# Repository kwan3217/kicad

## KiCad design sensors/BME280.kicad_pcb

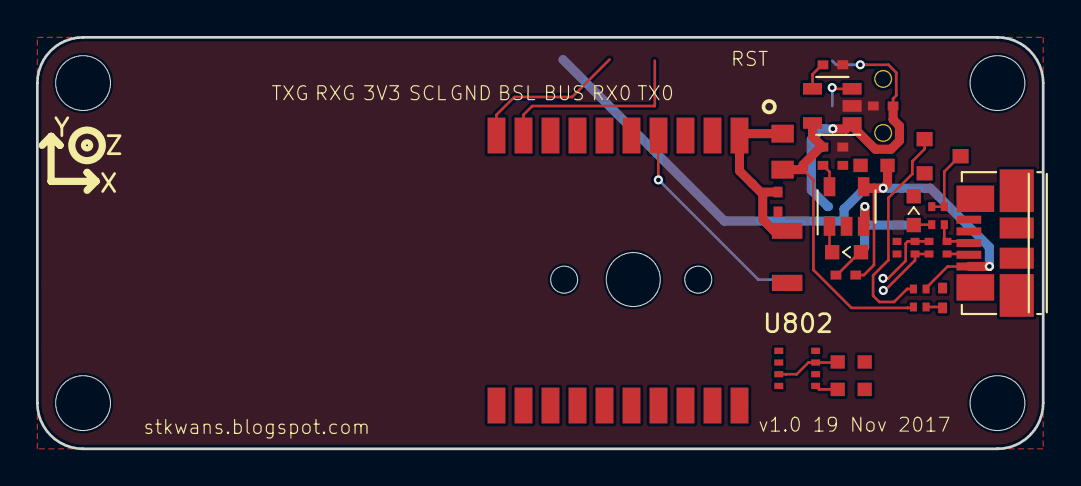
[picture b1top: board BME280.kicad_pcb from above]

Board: 2 copper layers, 55.9 x 22.9 mm, 34 parts (0 on the bottom side), 22 nets.

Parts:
B504: Coin_Cell; CR1220-2
C501, C714: 100nF; SMD_0402
C503: 10uF; SMD_1206
C623: 22pF; R_Array_Convex_2x0402
C704: 1uF; SMD_0402
C715: 4.7nF; SMD_0402
C802, C803: 4.7uF; SMD_0603
C806, C808: 100nF; SMD_0603
D650: BLUE; D_0603
D801: YELLOW; D_0603
D802: DCC; SOT-23
J601: USB_MICROB; USB_Micro-B_Molex_47346-0001
J801: JST 2mm; SPARKFUN_JST_POWER
JP1, JP2, JP4, JP5: STAND-OFFTIGHT; STAND-OFF-TIGHT
L501: Ferrite; SMD_0805
Q650: PMOS; SOT-23
R611: 22k; SMD_0402
R623: 33; R_Array_Convex_2x0402
R650: 1.5k; R_Array_Convex_2x0402
R651: 10k; R_Array_Convex_2x0402
R801: 10k; SMD_0402
R804: 1.5k; SMD_0402
S701: SPDT; SWITCH_DPDT_AZY0202
U501: FGPMMOPA6H
U599: FGPMMOPA6H; Axis
U701: 3.3V; SOT-23-5
U801: MCP73831; SOT-23-5
U802: BME280

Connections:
/CONNECT: Q650.1, R651.4
/CONN_D+: J601.3, R623.4, R650.4
/CONN_D-: J601.2, R623.3
/D+: C623.2, R623.1
/D-: C623.1, R623.2
/GND: B504.-, C501.1, C503.1, C623.3, C623.4, C802.2, C803.2, C806.1, C808.1, D650.1, J601.5, J601.6, J801.-, R611.1, R801.1, U501.3, U501.8, U501.12, U501.19, U801.2, U802.1, U802.5, U802.7
/ON: R611.2, R651.2
/PROG: R801.2, U801.5
/Regulator/BYP: C714.1, U701.4
/Regulator/PWR_EN: S701.2, U701.3
/STAT+: D801.2, R804.2
/STAT-: D801.1, U801.1
/USB_LIGHT+: Q650.3, R650.1, R650.2
/USB_LIGHT-: D650.2, R650.3
/VBACKUP: B504.+, U501.4
/VBUS: C802.1, D802.1, J601.1, R651.3, R804.1, U801.4
/VCC: C806.2, C808.2, U802.2, U802.6, U802.8
/VGPS: C501.2, C503.2, L501.2, U501.1
/VLIPO: C803.1, D802.2, J801.+, U801.3
/VRAW: C704.1, D802.3, S701.1, U701.1
GND: C704.2, C714.2, C715.2, S701.3, U701.2
VCC: C715.1, L501.1, R651.1, U701.5

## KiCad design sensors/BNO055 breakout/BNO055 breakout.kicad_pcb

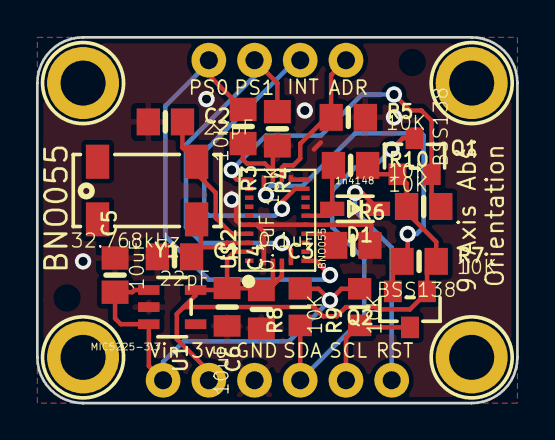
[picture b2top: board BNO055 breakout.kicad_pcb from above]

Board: 2 copper layers, 26.7 x 20.3 mm, 26 parts (0 on the bottom side), 16 nets.

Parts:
C1, C2: 22pF; 0805-NO
C3: 0.1uF; 0805-NO
C4: 0.1uF; 0805_10MGAP
C5: 10uF; 0805-NO
C6: 10uF; 0805_10MGAP
D1: 1n4148; SOD-323
JP1: 1X06_ROUND_76
JP2: 1X04_ROUND_76
Q1, Q2: BSS138; SOT23-WIDE
R3, R4, R5, R6, R7, R10: 10K; 0805-NO
R8, R9: 10K; _0805MP
U1: MIC5225-3.3; SOT23-5
U$2: BNO055
U$29, U$30, U$31, U$32: MOUNTINGHOLE2.5_THICK; MOUNTINGHOLE_2.5_PLATED_THICK
Y1: 32.768kHz; CRYSTAL_8X3.8

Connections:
3.3V: C4.2, C6.1, JP1.2, Q1.1, Q2.1, R6.2, R7.2, R10.2, U1.5, U$2.3, U$2.4, U$2.28
5.0V: C5.1, JP1.1, R8.2, R9.2, U1.1, U1.3
GND: C1.1, C2.1, C3.1, C4.1, C5.2, C6.2, JP1.3, R3.2, R4.2, R5.2, U1.2, U$2.2, U$2.10, U$2.15, U$2.16, U$2.18, U$2.25
I2CADDR_3V: JP2.4, R5.1, U$2.17
INT_3V: JP2.3, U$2.14
unnamed: C1.2, U$2.27, Y1.P$4
unnamed: C2.2, U$2.26, Y1.P$1
unnamed: C3.2, U$2.9
NRESET_3V: D1.A, R10.1, U$2.11
PS0_3V: JP2.1, R3.1, U$2.6
PS1_3V: JP2.2, R4.1, U$2.5
RST_5V: D1.C, JP1.6
SCL_3V: Q2.2, R7.1, U$2.19
SCL_5V: JP1.5, Q2.3, R9.1
SDA_3V: Q1.2, R6.1, U$2.20
SDA_5V: JP1.4, Q1.3, R8.1
